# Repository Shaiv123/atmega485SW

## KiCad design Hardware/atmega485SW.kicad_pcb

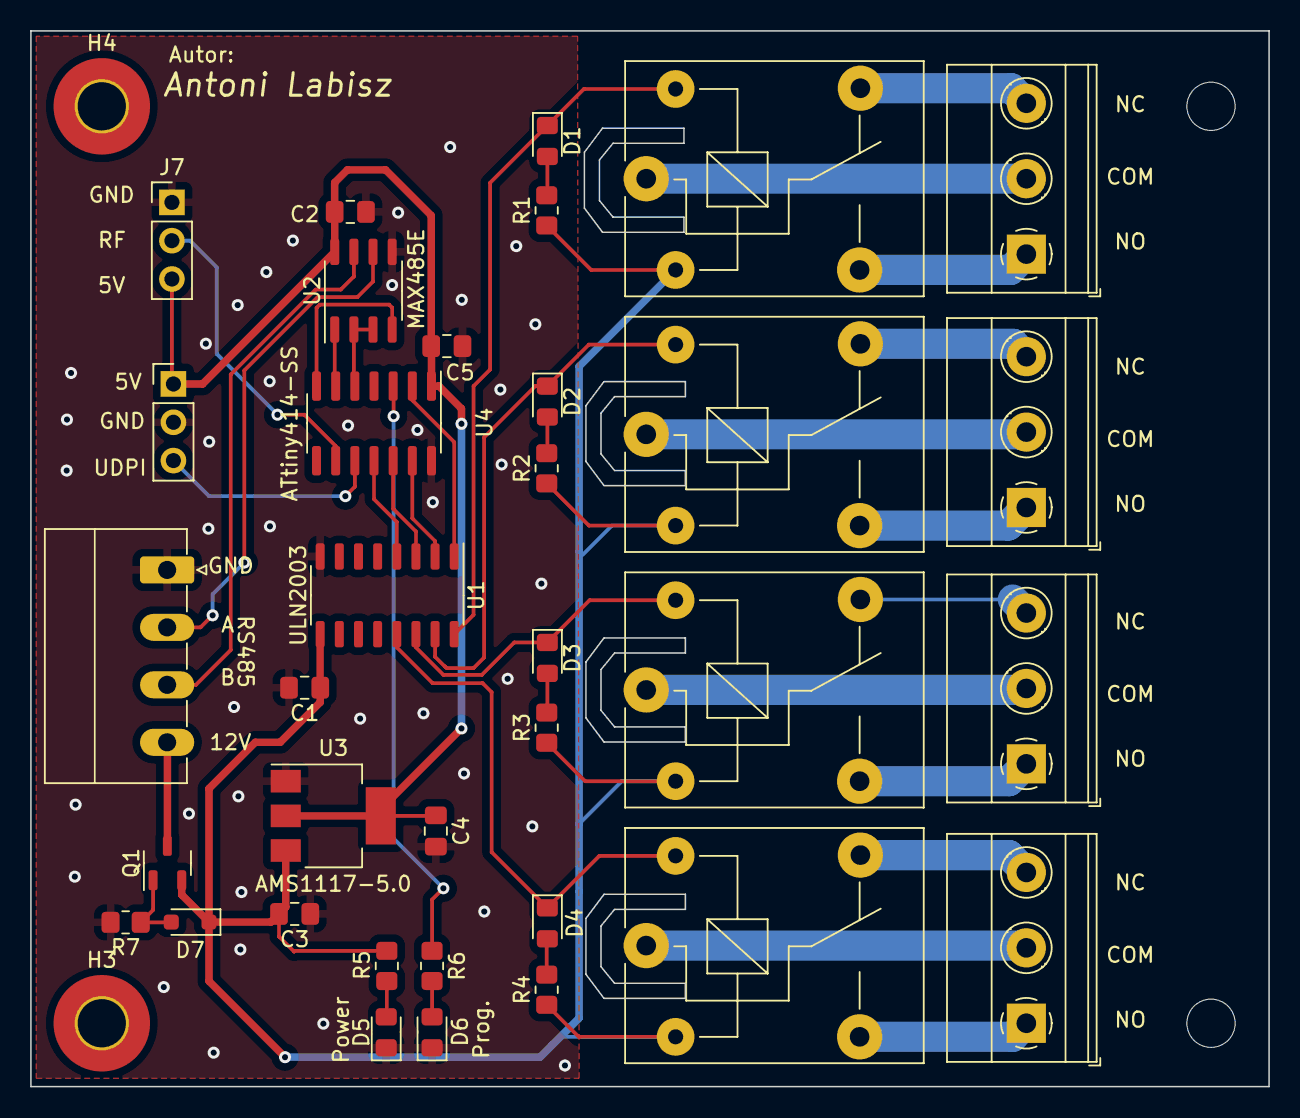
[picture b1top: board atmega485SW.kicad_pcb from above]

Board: 2 copper layers, 82.1 x 70.0 mm, 39 parts (0 on the bottom side), 39 nets.

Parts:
C1, C2, C5: 100n; C_0805_2012Metric_Pad1.18x1.45mm_HandSolder
C3, C4: 22u; C_0805_2012Metric_Pad1.18x1.45mm_HandSolder
D1, D2, D3, D4, D5, D6: LED_Small; LED_0805_2012Metric_Pad1.15x1.40mm_HandSolder
D7: 13V; D_SOD-323_HandSoldering
H1, H2: MountingHole; MountingHole_3.2mm_M3
H3, H4: MountingHole; MountingHole_3.2mm_M3_Pad_TopBottom
J1, J2, J3, J4: Screw_Terminal_01x03; TerminalBlock_Phoenix_MKDS-1,5-3_1x03_P5.00mm_Horizontal
J5: Screw_Terminal_01x04; PhoenixContact_MC_1,5_4-G-3.81_1x04_P3.81mm_Horizontal
J6, J7: Conn_01x03; PinHeader_1x03_P2.54mm_Vertical
K1, K2, K3, K4: SANYOU_SRD_Form_C; Relay_SPDT_SANYOU_SRD_Series_Form_C
Q1: AO3407A; SOT-23-3
R1, R2, R3, R4, R5, R6: 1k; R_0805_2012Metric_Pad1.20x1.40mm_HandSolder
R7: 10k; R_0805_2012Metric_Pad1.20x1.40mm_HandSolder
U1: ULN2003; SO-16_3.9x9.9mm_P1.27mm
U2: MAX485E; SO-8_3.9x4.9mm_P1.27mm
U3: AMS1117-5.0; SOT-223-3_TabPin2
U4: ATtiny414-SS; SOIC-14_3.9x8.7mm_P1.27mm

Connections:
+5V: C2.2, C4.1, C5.2, J6.1, J7.3, U2.8 (VCC), U3.2 (VO), U4.1 (VCC)
+12V: C1.1, C3.2, D7.1 (K), K1.2, K2.2, K3.2, K4.2, Q1.2 (S), R1.1, R2.1, R3.1, R4.1, R5.1, U1.9 (COM), U3.3 (VI)
+12VA: J5.4, Q1.3 (D)
A: J5.2, U2.6 (A)
A1: U1.4 (I4), U4.11 (PA1)
A2: U1.3 (I3), U4.12 (PA2)
A3: U1.2 (I2), U4.13 (PA3)
A4: U1.1 (I1), U4.2 (PA4)
A5: R6.1, U4.3 (PA5)
B: J5.3, U2.7 (B)
GND: C1.2, C2.1, C3.1, C4.2, C5.1, D5.1 (K), D6.1 (K), J5.1, J6.2, J7.1, R7.2, U1.8 (GND), U2.5 (GND), U3.1 (GND), U4.14 (GND)
K1: D1.1 (K), K1.5, U1.16 (O1)
K2: D2.1 (K), K2.5, U1.15 (O2)
K3: D3.1 (K), K3.5, U1.14 (O3)
K4: D4.1 (K), K4.5, U1.13 (O4)
unnamed: D1.2 (A), R1.2
unnamed: D2.2 (A), R2.2
unnamed: D3.2 (A), R3.2
unnamed: D4.2 (A), R4.2
unnamed: D5.2 (A), R5.2
unnamed: D6.2 (A), R6.2
unnamed: D7.2 (A), Q1.1 (G), R7.1
unnamed: J1.1, K1.3
unnamed: J1.2, K1.1
unnamed: J1.3, K1.4
unnamed: J2.1, K2.3
unnamed: J2.2, K2.1
unnamed: J2.3, K2.4
unnamed: J3.1, K3.3
unnamed: J3.2, K3.1
unnamed: J3.3, K3.4
unnamed: J4.1, K4.3
unnamed: J4.2, K4.1
unnamed: J4.3, K4.4
RE/DE: U2.2 (~RE), U2.3 (DE), U4.5 (PA7)
RF: J7.2, U4.9 (PB0)
RX: U2.1 (RO), U4.6 (PB3)
TX: U2.4 (DI), U4.7 (PB2)
UDPI: J6.3, U4.10 (~RESET/PA0)

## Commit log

2024-10-13 Initial
